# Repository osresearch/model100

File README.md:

TRS-80 Model iCE100
====

This replaces the mainboard of the TRS-80 Model 100 with an iCE40 FPGA
(or with limited features using a Teensy++) that can act as a serial or
graphics console to a USB attached device.

More info: https://trmm.net/TRS80_Model_100

Pinout
===

The LCD is 240x64 and uses ten Hitachi HD44102 LCD controllers,
each with its own select line and shared control lines.

The LCD requires a charge pump to generate the -5V required for the bias
voltage.  This is generated with a duty cycle controlled PWM output.

LCD connector HU-30P-2G-L13

Pin | Function
----|---------
  1 | VDD
  2 | BZ - buzzer on the front panel (optional)
  3 | VEE -- negative voltage (-5V)
  4 | V2 - contrast voltage (0 - 5V)
  5 | GND
  6 | GND
  7 | CS24
  8 | CS23
  9 | CS29
 10 | CS22
 11 | CS28
 12 | CS21
 13 | CS27
 14 | CS20
 15 | CS26
 16 | CS25
 17 | RESET (can be pulled high for always reset)
 18 | CS1
 19 | E
 20 | R/!W (can be pulled low for always write)
 21 | D/!I
 22 | AD0
 23 | AD1
 24 | AD2
 25 | AD3
 26 | AD4
 27 | AD5
 28 | AD6
 29 | AD7
 30 | NC

LCD bias voltage
===

The LCD requires negative voltage, which is generated with a two diode,
two capacitor charge pump.

           +
    PWM ---||---+--|<--+-- OUT
                |      |
                \/    ---
                --    ---+
                |      |
    GND --------+------+

If it is driven with a 3V signal, the minimum output is around -2 V.
Driving with a 5V PWM produces  -3 V, which gives better contrast.

            5V
             |
             # 100 Ohm
             |
             +-------------- 5V PWM out
             |
             /
    PWM ----|
             \
             v
             |
            GND        

Image format
===

    convert -resize !240x64 -depth 1 -monochrome -rotate 90 \
	logo.png logo.gray
    xxd -g8 -c8 -p logo.gray > fb.hex

Keyboard
====

The 8x9 keyboard matrix has diodes on every key so it is possible to
identify any number of pressed keys.  However, due to the direction of
the diodes this requires that a slightly odd mechanism be used.

The 8 rows are all configured as input pullups and the 8 of the 9 columns
are driven high.  All the rows are read and any that have been pulled low
due to the diode sinking current to ground are pressed.

          3V
           |
           # internal pullup
           |
    Row ---+---->|--/ --- Col

Upduino v2
===

J6 1.7 5 90
JP6 39.5 1.8 180
JP5 39.5 19.58 180

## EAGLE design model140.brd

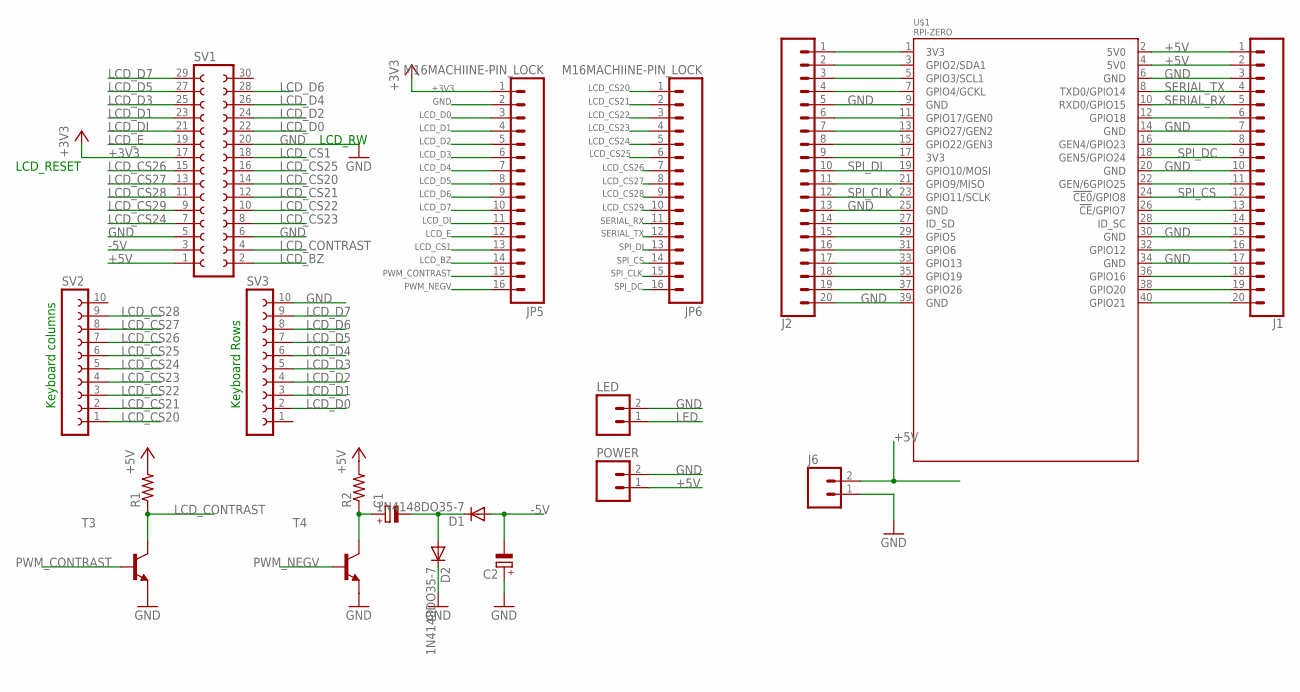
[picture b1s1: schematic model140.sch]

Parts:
C1, C2: CPOL-EUE2.5-7; E2,5-7
D1, D2: 1N4148DO35-7; DO35-7
J1, J2: CONN_20; 1X20
J6: M02PTH; 1X02
JP5, JP6: M16MACHIINE-PIN_LOCK; 1X16_MACHINE-PIN-HEADER_LOCK.004@1
LED: M02PTH; 1X02
POWER: M02PTH; 1X02
R1, R2: R-US_0204/5; 0204/5
SV1: FE15-2
SV2, SV3: FE10W
T3, T4: MPS2222A-NPN-TO92-CBE; TO92-CBE
U$1: RPI-ZERO; RASP_PI_ZERO_BOARD_FULL

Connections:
3V3@1: J2.1, U$1.1 (3V3)
3V3@2: J2.9, U$1.17 (3V3)
+3V3: JP5.1, SV1.17
+5V: J1.1, J1.2, J6.2, POWER.1, R1.2, R2.2, SV1.1, U$1.2 (5V0), U$1.4 (5V0)
-5V: C2.-, D1.A, SV1.3
GND: C2.+, D2.C, J1.3, J1.7, J1.10, J1.15, J1.17, J2.5, J2.13, J2.20, J6.1, JP5.2, LED.2, POWER.2, SV1.5, SV1.6, SV1.20, SV3.10, T3.E, T4.E, U$1.6 (GND), U$1.9 (GND), U$1.14 (GND), U$1.20 (GND), U$1.25 (GND), U$1.30 (GND), U$1.34 (GND), U$1.39 (GND)
LCD_BZ: JP5.14, SV1.2
LCD_CONTRAST: R1.1, SV1.4, T3.C
LCD_CS1: JP5.13, SV1.18
LCD_CS20: JP6.1, SV1.14, SV2.1
LCD_CS21: JP6.2, SV1.12, SV2.2
LCD_CS22: JP6.3, SV1.10, SV2.3
LCD_CS23: JP6.4, SV1.8, SV2.4
LCD_CS24: JP6.5, SV1.7, SV2.5
LCD_CS25: JP6.6, SV1.16, SV2.6
LCD_CS26: JP6.7, SV1.15, SV2.7
LCD_CS27: JP6.8, SV1.13, SV2.8
LCD_CS28: JP6.9, SV1.11, SV2.9
LCD_CS29: JP6.10, SV1.9
LCD_D0: JP5.3, SV1.22, SV3.2
LCD_D1: JP5.4, SV1.23, SV3.3
LCD_D2: JP5.5, SV1.24, SV3.4
LCD_D3: JP5.6, SV1.25, SV3.5
LCD_D4: JP5.7, SV1.26, SV3.6
LCD_D5: JP5.8, SV1.27, SV3.7
LCD_D6: JP5.9, SV1.28, SV3.8
LCD_D7: JP5.10, SV1.29, SV3.9
LCD_DI: JP5.11, SV1.21
LCD_E: JP5.12, SV1.19
LED: LED.1
unnamed: J2.2, U$1.3 (GPIO2/SDA1)
unnamed: J2.3, U$1.5 (GPIO3/SCL1)
unnamed: J2.4, U$1.7 (GPIO4/GCKL)
unnamed: J2.6, U$1.11 (GPIO17/GEN0)
unnamed: J2.7, U$1.13 (GPIO27/GEN2)
unnamed: J2.8, U$1.15 (GPIO22/GEN3)
unnamed: J2.11, U$1.21 (GPIO9/MISO)
unnamed: J2.14, U$1.27 (ID_SD)
unnamed: J2.15, U$1.29 (GPIO5)
unnamed: J2.16, U$1.31 (GPIO6)
unnamed: J2.17, U$1.33 (GPIO13)
unnamed: J2.18, U$1.35 (GPIO19)
unnamed: J2.19, U$1.37 (GPIO26)
unnamed: J1.20, U$1.40 (GPIO21)
unnamed: J1.19, U$1.38 (GPIO20)
unnamed: J1.18, U$1.36 (GPIO16)
unnamed: J1.16, U$1.32 (GPIO12)
unnamed: J1.14, U$1.28 (ID_SC)
unnamed: J1.13, U$1.26 (!CE!/GPIO7)
unnamed: J1.11, U$1.22 (GEN/6GPIO25)
unnamed: J1.8, U$1.16 (GEN4/GPIO23)
unnamed: J1.6, U$1.12 (GPIO18)
unnamed: C1.+, R2.1, T4.C
unnamed: C1.-, D1.C, D2.A
PWM_CONTRAST: JP5.15, T3.B
PWM_NEGV: JP5.16, T4.B
SERIAL_RX: J1.5, JP6.11, U$1.10 (RXD0/GPIO15)
SERIAL_TX: J1.4, JP6.12, U$1.8 (TXD0/GPIO14)
SPI_CLK: J2.12, JP6.15, U$1.23 (GPIO11/SCLK)
SPI_CS: J1.12, JP6.14, U$1.24 (!CE0!/GPIO8)
SPI_DC: J1.9, JP6.16, U$1.18 (GEN5/GPIO24)
SPI_DI: J2.10, JP6.13, U$1.19 (GPIO10/MOSI)

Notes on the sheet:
Keyboard Rows
Keyboard columns
LCD_RW
LCD_RESET

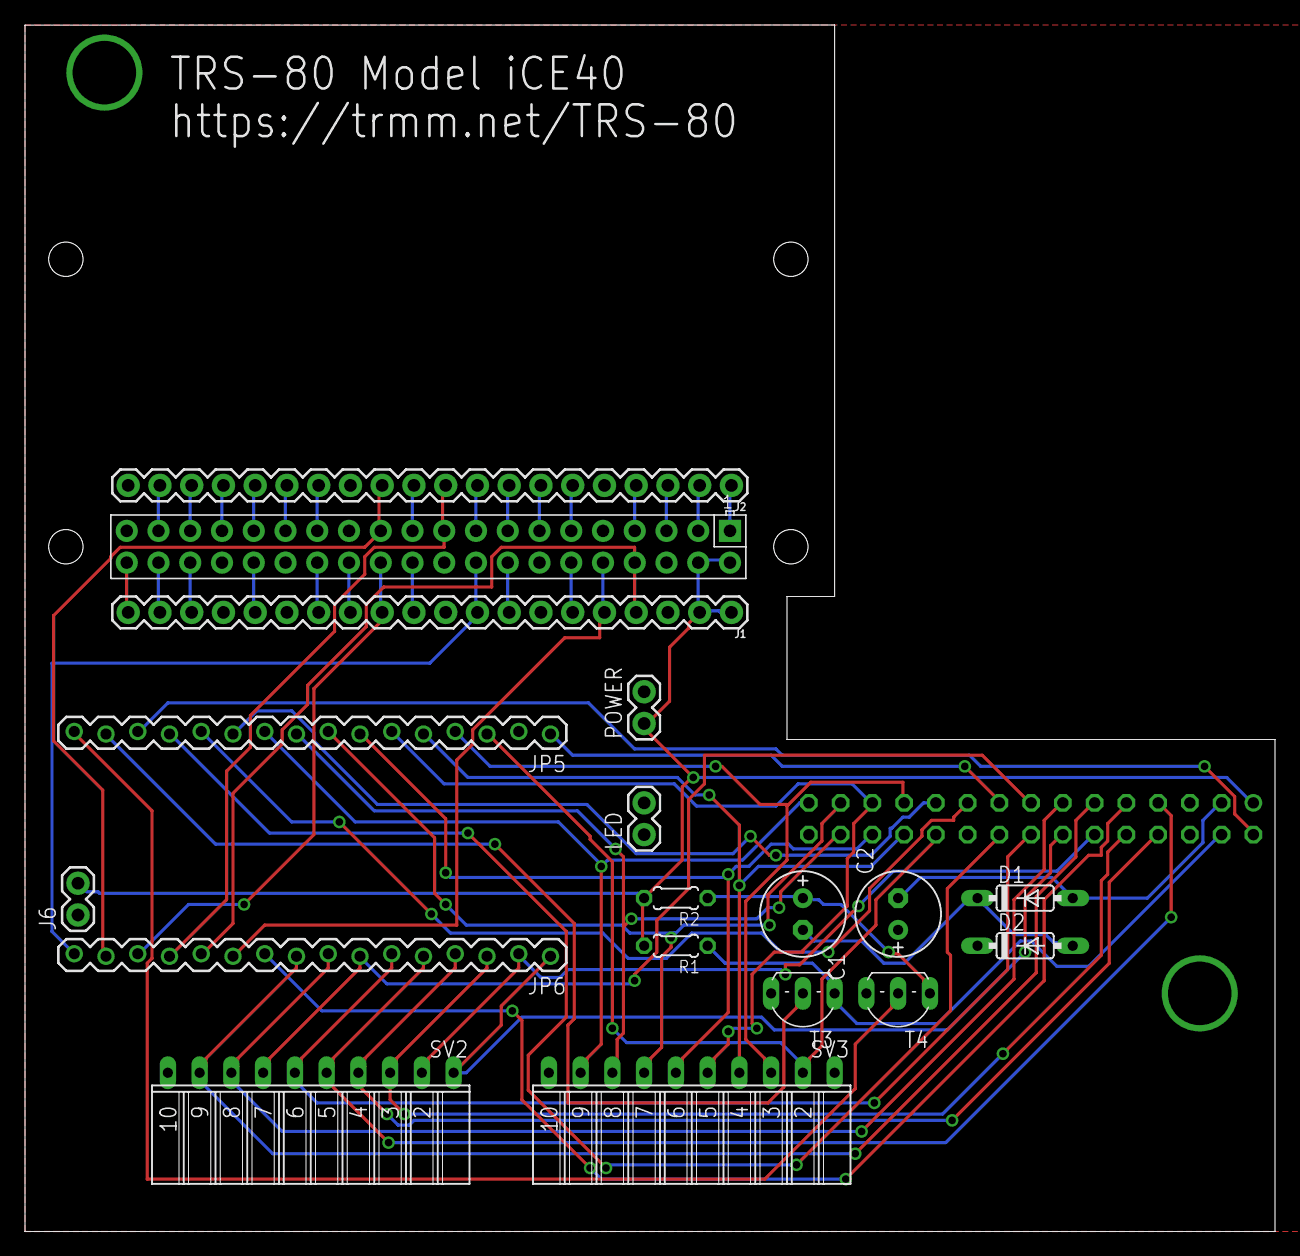
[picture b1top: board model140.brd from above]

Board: 2 copper layers, 100.0 x 96.5 mm, 19 parts (1 on the bottom side), 61 nets.

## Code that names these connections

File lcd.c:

/**
 * \file HD44102 driver
 *
 * Preparation for Model 100 retrofit
 *
 * CS1 is tied to ground on all chips.
 * CS2 is exposed per chip
 * CS3 is common to all chips, named CS1 on schematic
 * 
 * To select a chip, CS2 and CS3 must be high
 *
 * In write mode, data is latched on the fall of LCD_EN
 * LCD_DI high == data, low == command
 *
 * Keep free:
 * i2c: PD0, PD1
 * RS232: PD2, PD3
 * SPI: PB3, PB2, PB1, PB0
 */

#include <avr/io.h>
#include <avr/pgmspace.h>
#include <avr/interrupt.h>
#include <avr/eeprom.h>
#include <stdint.h>
#include <string.h>
#include <util/delay.h>
#include "bits.h"
#include "lcd.h"

#define LCD_V2		0xB7 // 4, Analog voltage to generate negative voltage
#define LCD_VO		0xB6 // Analog voltage to control contrast
#define LCD_RESET	0xD4 // 17
#define LCD_CS1		0xD5 // 18
#define LCD_EN		0xE0 // 19
#define LCD_RW		0xD7 // 20
#define LCD_DI		0xE1 // 21
#define LCD_BZ		0xB5 // 2

#define LCD_DATA_PORT	PORTC // 22-29
#define LCD_DATA_PIN	PINC
#define LCD_DATA_DDR	DDRC

#define LCD_CS20	0xF0
#define LCD_CS21	0xF1
#define LCD_CS22	0xF2
#define LCD_CS23	0xF3
#define LCD_CS24	0xF4
#define LCD_CS25	0xF5
#define LCD_CS26	0xF6
#define LCD_CS27	0xF7
#define LCD_CS28	0xE6
#define LCD_CS29	0xE7


static uint8_t
lcd_command(
	const uint8_t byte,
	const uint8_t di, // 0 == instruction, 1 == data
	const uint8_t write_dir
)
{
	uint8_t rc = 0;

	out(LCD_DI, di);
	out(LCD_RW, !write_dir); // write
	if (write_dir)
	{
		out(LCD_EN, 1);
		LCD_DATA_DDR = 0xFF;
	} else {
		LCD_DATA_DDR = 0x00; // inputs
		LCD_DATA_PORT = 0x00; // no pull ups
		out(LCD_EN, 1);
	}

	if (write_dir)
	{
		_delay_us(2);
		LCD_DATA_PORT = byte;
	} else {
		_delay_us(2);
		rc = LCD_DATA_PIN;
	}

	_delay_us(2);
	out(LCD_EN, 0);

	// value has been sent, go into read mode
	_delay_us(2);
	LCD_DATA_PORT = 0x00; // no pull ups
	LCD_DATA_DDR = 0x00;

	out(LCD_DI, 0); // status command
	out(LCD_RW, 1); // read

	out(LCD_EN, 1);
	_delay_us(10);
	if (write_dir)
		rc = LCD_DATA_PIN;
	out(LCD_EN, 0);

	// Everything looks good.
	out(LCD_RW, 0); // go back into write mode
	return rc;
}



static void
lcd_vee(
	uint16_t x
)
{
	OCR1C = x;
}


static void
lcd_contrast(
	uint16_t x
)
{
	OCR1B = x;
}


static void
lcd_on(
	const uint8_t pin
)
{
	out(pin, 1);

	// Turn on display
	lcd_command(0x39, 0, 1);
	_delay_ms(1);

	// Up mode
	lcd_command(0x3B, 0, 1);
	_delay_ms(1);

	// Start at location 0
	lcd_command(0x00, 0, 1);
	_delay_ms(1);

	// Display start page 0
	lcd_command(0x3E, 0, 1);
	_delay_ms(1);

	out(pin, 0);
}


void
lcd_init(void)
{
	LCD_DATA_PORT = 0x00;
	LCD_DATA_DDR = 0x00;

	out(LCD_DI, 0);
	out(LCD_RW, 0);
	out(LCD_EN, 0);
	out(LCD_V2, 0);
	out(LCD_VO, 0);
	out(LCD_DI, 0);
	out(LCD_CS1, 0);
	out(LCD_CS20, 0);
	out(LCD_CS21, 0);
	out(LCD_CS22, 0);
	out(LCD_CS23, 0);
	out(LCD_CS24, 0);
	out(LCD_CS25, 0);
	out(LCD_CS26, 0);
	out(LCD_CS27, 0);
	out(LCD_CS28, 0);
	out(LCD_CS29, 0);
	out(LCD_RESET, 0);
	out(LCD_BZ, 0);

	ddr(LCD_DI, 1);
	ddr(LCD_RW, 1);
	ddr(LCD_EN, 1);
	ddr(LCD_V2, 1);
	ddr(LCD_VO, 1);
	ddr(LCD_CS1, 1);
	ddr(LCD_RESET, 1);
	ddr(LCD_BZ, 1);

	ddr(LCD_CS20, 1);
	ddr(LCD_CS21, 1);
	ddr(LCD_CS22, 1);
	ddr(LCD_CS23, 1);
	ddr(LCD_CS24, 1);
	ddr(LCD_CS25, 1);
	ddr(LCD_CS26, 1);
	ddr(LCD_CS27, 1);
	ddr(LCD_CS28, 1);
	ddr(LCD_CS29, 1);


	// Configure OC1x in fast-PWM mode, 10-bit
	sbi(TCCR1B, WGM12);
	sbi(TCCR1A, WGM11);
	sbi(TCCR1A, WGM10);

	// OC1C is used to generate the Vee via a charge pump
	// Configure output mode to clear on match, set at top
	sbi(TCCR1A, COM1C1);
	cbi(TCCR1A, COM1C0);

	// OC1B is used to control brightness via PWM
	// Configure output mode to clear on match, set at top
	sbi(TCCR1A, COM1B1);
	cbi(TCCR1A, COM1B0);

	// Configure clock 1 at clk/1
	cbi(TCCR1B, CS12);
	cbi(TCCR1B, CS11);
	sbi(TCCR1B, CS10);

	lcd_vee(0x100); // 50% duty cycle
	lcd_contrast(0x280); // almost +5V
	
	_delay_ms(20);

	// Raise the reset line, to bring the chips online
	out(LCD_RESET, 1);

	// Raise the master select line, since we always want to talk to
	// all chips.  We leave it up since we'll be asserting each one
	// individually in a little while.
	out(LCD_CS1, 1);

	lcd_on(LCD_CS20);
	lcd_on(LCD_CS21);
	lcd_on(LCD_CS22);
	lcd_on(LCD_CS23);
	lcd_on(LCD_CS24);
	lcd_on(LCD_CS25);
	lcd_on(LCD_CS26);
	lcd_on(LCD_CS27);
	lcd_on(LCD_CS28);
	lcd_on(LCD_CS29);

	// Bring LCD select back down since we don't want to
	// talk to the LCD while strobing the keyboard.
	out(LCD_CS1, 0);
}


/** Enable the one chip, select the address and send/recv the byte.
 *
 * x goes from 0 to 50, y goes from 0 to 32, rounded to 8.
 */
static void
lcd_bulk_write(
	const uint8_t pin,
	uint8_t x,
	uint8_t y,
	const uint8_t * buf,
	uint8_t n
)
{
	out(pin, 1);
	lcd_command((y >> 3) << 6 | x, 0, 1);

	for (uint8_t i = 0 ; i < n ; i++)
		lcd_command(buf[i], 1, 1);

	out(pin, 0);
}


/** Display val at position x,y.
 *
 * x is ranged 0 to 240, for each pixel
 * y is ranged 0 to 64, rounded to 8
 */
void
lcd_write(
	uint8_t x,
	uint8_t y,
	const uint8_t * buf,
	uint8_t n
)
{
	out(LCD_CS1, 1);

	if (y < 32)
	{
		// Top half of the display
		if (x < 50)
			lcd_bulk_write(LCD_CS20, x - 0, y - 0, buf, n);
		else
		if (x < 100)
			lcd_bulk_write(LCD_CS21, x - 50, y - 0, buf, n);
		else
		if (x < 150)
			lcd_bulk_write(LCD_CS22, x - 100, y - 0, buf, n);
		else
		if (x < 200)
			lcd_bulk_write(LCD_CS23, x - 150, y - 0, buf, n);
		else
			lcd_bulk_write(LCD_CS24, x - 200, y - 0, buf, n);
	} else {
		// Bottom half of the display
		if (x < 50)
			lcd_bulk_write(LCD_CS25, x - 0, y - 32, buf, n);
		else
		if (x < 100)
			lcd_bulk_write(LCD_CS26, x - 50, y - 32, buf, n);
		else
		if (x < 150)
			lcd_bulk_write(LCD_CS27, x - 100, y - 32, buf, n);
		else
		if (x < 200)
			lcd_bulk_write(LCD_CS28, x - 150, y - 32, buf, n);
		else
			lcd_bulk_write(LCD_CS29, x - 200, y - 32, buf, n);
	}

	out(LCD_CS1, 0);
}


/** Enable the one chip, select the address and send/recv the byte.
 *
 * x goes from 0 to 50, y goes from 0 to 32, rounded to 8.
 */
static void
lcd_bulk_read(
	const uint8_t pin,
	uint8_t x,
	uint8_t y,
	uint8_t * buf,
	uint8_t n
)
{
	out(pin, 1);
	lcd_command((y >> 3) << 6 | x, 0, 1);
	lcd_command(0, 1, 0); // dummy

	for (int i = 0 ; i < n ; i++)
		buf[i] = lcd_command(0, 1, 0);
	out(pin, 0);
}


void
lcd_read(
	uint8_t x,
	uint8_t y,
	uint8_t * buf,
	uint8_t n
)
{
	out(LCD_CS1, 1);

	if (y < 32)
	{
		// Top half of the display
		if (x < 50)
			lcd_bulk_read(LCD_CS20, x - 0, y - 0, buf, n);
		else
		if (x < 100)
			lcd_bulk_read(LCD_CS21, x - 50, y - 0, buf, n);
		else
		if (x < 150)
			lcd_bulk_read(LCD_CS22, x - 100, y - 0, buf, n);
		else
		if (x < 200)
			lcd_bulk_read(LCD_CS23, x - 150, y - 0, buf, n);
		else
			lcd_bulk_read(LCD_CS24, x - 200, y - 0, buf, n);
	} else {
		// Bottom half of the display
		if (x < 50)
			lcd_bulk_read(LCD_CS25, x - 0, y - 32, buf, n);
		else
		if (x < 100)
			lcd_bulk_read(LCD_CS26, x - 50, y - 32, buf, n);
		else
		if (x < 150)
			lcd_bulk_read(LCD_CS27, x - 100, y - 32, buf, n);
		else
		if (x < 200)
			lcd_bulk_read(LCD_CS28, x - 150, y - 32, buf, n);
		else
			lcd_bulk_read(LCD_CS29, x - 200, y - 32, buf, n);
	}

	out(LCD_CS1, 0);
}

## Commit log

2012-11-22 4-bit LCD driver works
2012-11-28 import from busybox vi.c
2012-11-28 adjust brightness more quickly
2012-11-30 hacks that sort of work
2012-11-30 conversion for the model100 lcd tests
2012-12-01 driver works, contrast sucks
2012-12-01 better default contrast
2012-12-01 all displays work!
2012-12-01 5x7 font
2012-12-01 still off by a bit
2012-12-01 send address each time; could be made faster
2012-12-01 started trying to scan keyboard
2012-12-02 key scanning mostly works
2012-12-03 key scaning works
2013-01-02 works with permaprotoboard design
2013-01-03 Default LCD Vee and contrast
2013-01-05 contrast and lcd works again!
2013-01-05 Bring down LCD_CS1 until we start sending again, and start scanning keyboard
2013-01-05 Key scan is almost working, some ghosting still
2013-01-05 scanning, caps and shift mostly works!
2013-01-05 Store separate shift table
2013-01-05 Caps works again
2013-01-05 Enable start page 0 on LCD and display typed text
2013-01-05 Moved key rows to PORTA
2013-01-05 Added tag everything-works for changeset edd2d809a62d
2013-01-06 fix m
2013-01-06 vt100 is coming along... clear works
2013-01-06 backspace works
2013-01-06 arrow keys and lynx almost work!
2013-01-06 inverse works
2013-01-06 Use mode 7 for inverse video; should add underline and others
2013-01-06 split into separate files, improved underline/inverse video
2013-01-06 remove extraneous comments
2013-03-10 Serial talks to the raspberry pi! need to add scrolling
2013-03-10 Correct sense of UDRE1 -- serial console works!
2013-03-10 Scrolling almost works
2013-03-10 scrolling works, but painfully
2013-03-11 Support read/write contiguous blocks of LCD
2019-01-30 porting from AVR to FPGA
2019-01-31 LCD pinout, data sheets and images
2019-02-02 negative voltage output works
2019-02-02 lcd driver, not working yet
2019-02-02 nextpnr and all gpios
2019-02-02 fix sense of pwm
2019-02-03 fix direction of data pins
2019-02-03 fix sense of enable pin, do not try to select all modules at the same time
2019-02-03 LCD almost works
2019-02-03 correct pinout on cable
2019-02-03 correct dimension and cs pin switch at end of line
2019-02-03 flicker test shows slow redraw, otherwise stable
2019-02-03 logo drawing work
2019-02-04 convert LCD to drive each module inturn, rather than an entire row at once
2019-02-04 started on "model140" interface board and analog components
2019-02-04 video playback over serial port works
2019-02-04 radioshack logo
2019-02-05 text buffer and buzzer works
2019-02-05 moved font code into separate module
2019-02-05 ignore hg and temp files
2019-02-05 shrink y output for 0-7
2019-02-05 move textbuffer code into separate module
2019-02-05 preparing for keyboard wiring
2019-02-06 allow usb dev to be overridden
2019-02-06 started on keyboard
2019-02-06 lcd frame strobe to coordinate access to lcd data pins with keyboard
2019-02-07 pi zero-w version with upduino v2
2019-02-07 add pi-zero header duplicate
2019-02-10 as ordered
2019-02-10 working on spi display interface
2019-02-10 spi display almost works!
2019-02-10 spi display device works!
2019-02-16 works with the model140 board
2020-03-02 add images
2020-09-14 move avr code into subdirectory
2020-09-14 move verilog code into subdir
2020-09-14 note that this is both teensy and verilog code now

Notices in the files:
parts and their libraries:
SparkFun-Connectors: Licensing: Creative Commons ShareAlike 4.0 International - https://creativecommons.org/licenses/by-sa/4.0
